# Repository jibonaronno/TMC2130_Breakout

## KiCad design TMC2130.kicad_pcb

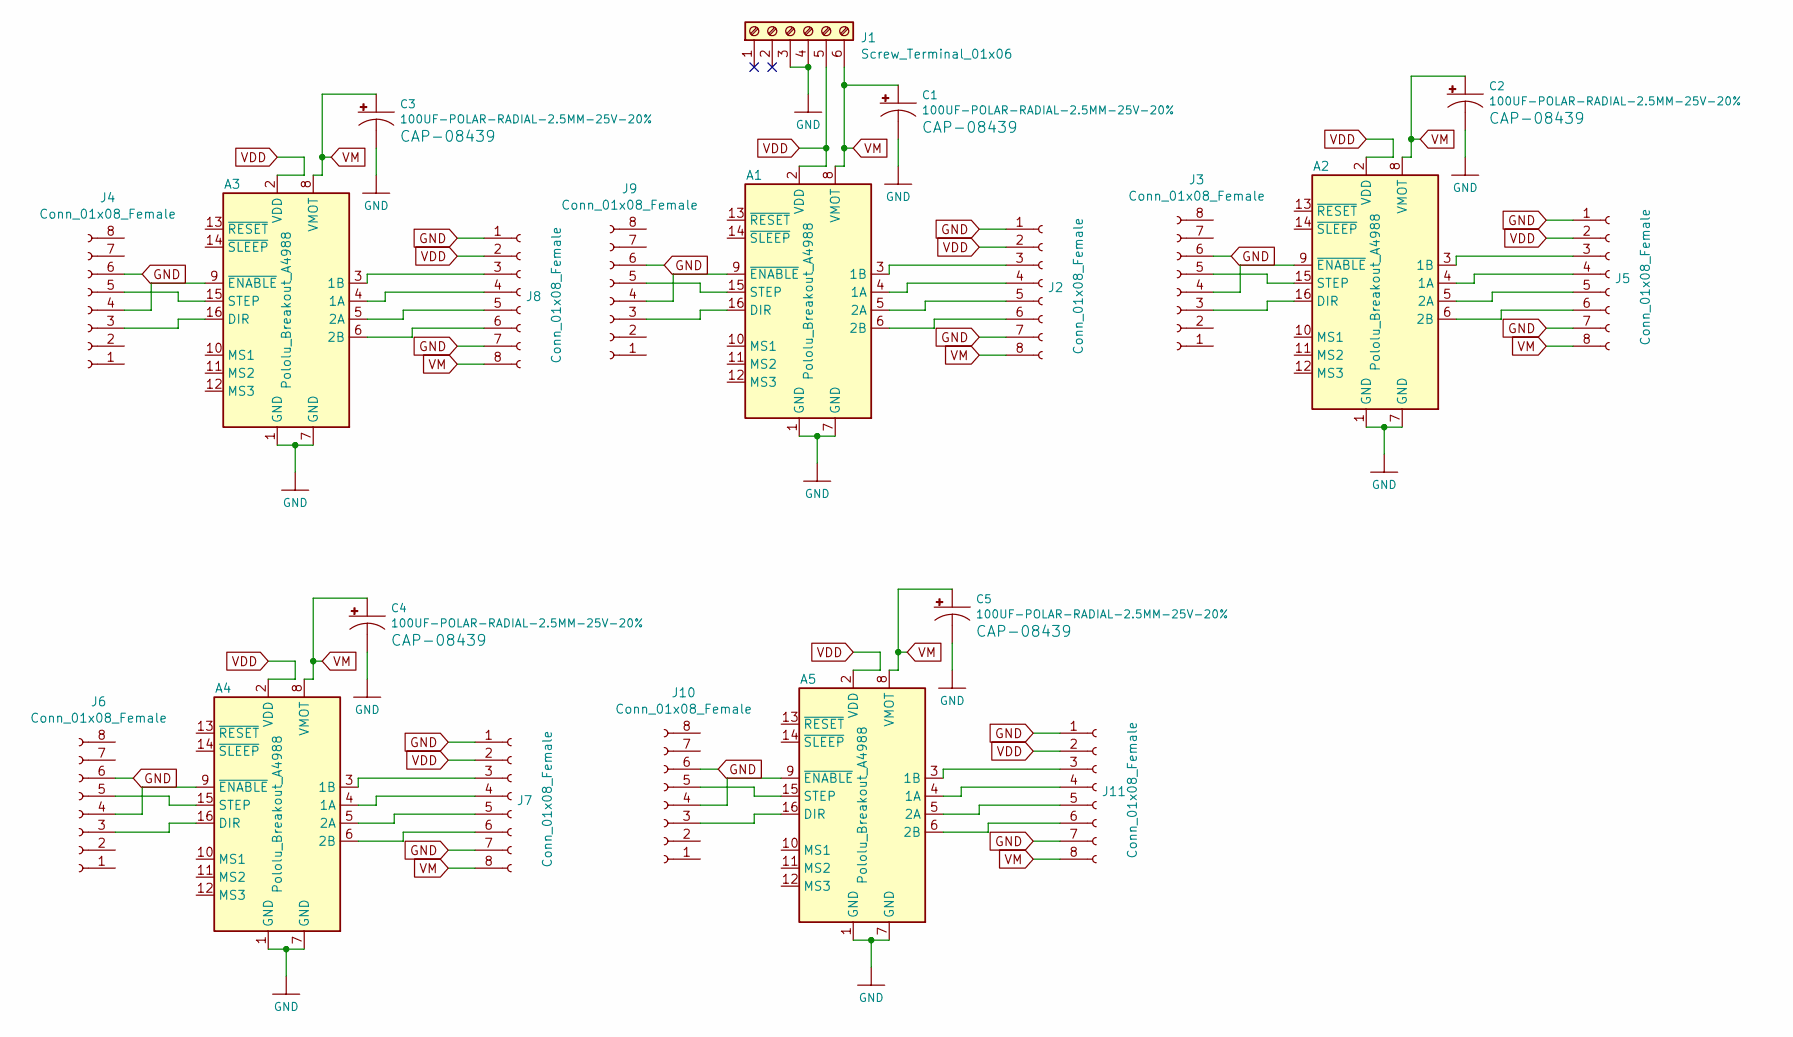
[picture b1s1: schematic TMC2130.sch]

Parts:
A1, A2, A3, A4, A5: Pololu_Breakout_A4988; Pololu_Breakout-16_15.2x20.3mm
C1, C2, C3, C4, C5: 100UF-POLAR-RADIAL-2.5MM-25V-20%; CPOL-RADIAL-2.5MM-6.5MM
J1: Screw_Terminal_01x06; TerminalBlock_MetzConnect_Type011_RT05506HBWC_1x06_P5.00mm_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
J2, J3, J4, J5, J6, J7, J8, J9, J10, J11: Conn_01x08_Female; JST_EH_B8B-EH-A_1x08_P2.50mm_Vertical

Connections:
GND: A1.1 (GND), A1.7 (GND), A2.1 (GND), A2.7 (GND), A3.1 (GND), A3.7 (GND), A4.1 (GND), A4.7 (GND), A5.1 (GND), A5.7 (GND), C1.2 (-), C2.2 (-), C3.2 (-), C4.2 (-), C5.2 (-), J1.3, J1.4, J2.1, J2.7, J3.6, J4.6, J5.1, J5.7, J6.6, J7.1, J7.7, J8.1, J8.7, J9.6, J10.6, J11.1, J11.7
unnamed: A1.3 (1B), J2.3
unnamed: A1.4 (1A), J2.4
unnamed: A1.5 (2A), J2.5
unnamed: A1.6 (2B), J2.6
unnamed: A1.9 (~ENABLE), J9.4
unnamed: A1.15 (STEP), J9.5
unnamed: A1.16 (DIR), J9.3
unnamed: A2.3 (1B), J5.3
unnamed: A2.4 (1A), J5.4
unnamed: A2.5 (2A), J5.5
unnamed: A2.6 (2B), J5.6
unnamed: A2.9 (~ENABLE), J3.4
unnamed: A2.15 (STEP), J3.5
unnamed: A2.16 (DIR), J3.3
unnamed: A3.3 (1B), J8.3
unnamed: A3.4 (1A), J8.4
unnamed: A3.5 (2A), J8.5
unnamed: A3.6 (2B), J8.6
unnamed: A3.9 (~ENABLE), J4.4
unnamed: A3.15 (STEP), J4.5
unnamed: A3.16 (DIR), J4.3
unnamed: A4.3 (1B), J7.3
unnamed: A4.4 (1A), J7.4
unnamed: A4.5 (2A), J7.5
unnamed: A4.6 (2B), J7.6
unnamed: A4.9 (~ENABLE), J6.4
unnamed: A4.15 (STEP), J6.5
unnamed: A4.16 (DIR), J6.3
unnamed: A5.3 (1B), J11.3
unnamed: A5.4 (1A), J11.4
unnamed: A5.5 (2A), J11.5
unnamed: A5.6 (2B), J11.6
unnamed: A5.9 (~ENABLE), J10.4
unnamed: A5.15 (STEP), J10.5
unnamed: A5.16 (DIR), J10.3
VDD: A1.2 (VDD), A2.2 (VDD), A3.2 (VDD), A4.2 (VDD), A5.2 (VDD), J1.5, J2.2, J5.2, J7.2, J8.2, J11.2
VM: A1.8 (VMOT), A2.8 (VMOT), A3.8 (VMOT), A4.8 (VMOT), A5.8 (VMOT), C1.1 (+), C2.1 (+), C3.1 (+), C4.1 (+), C5.1 (+), J1.6, J2.8, J5.8, J7.8, J8.8, J11.8

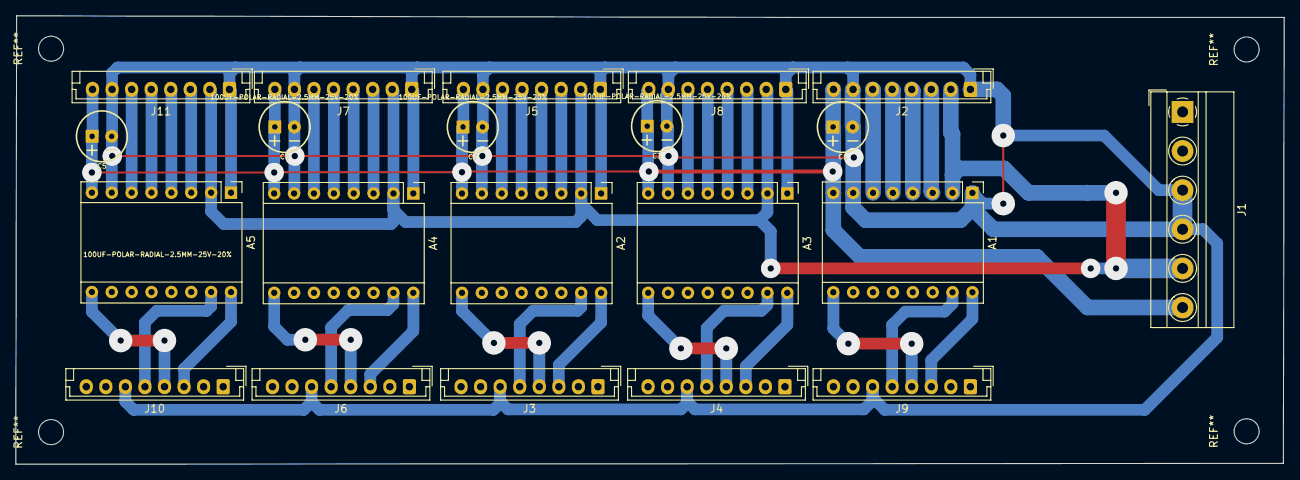
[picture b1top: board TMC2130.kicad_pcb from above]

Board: 2 copper layers, 162.1 x 57.3 mm, 21 parts (0 on the bottom side), 38 nets.

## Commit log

2020-09-25 FYSETC TMC2130 5 module breakout board kicad pcb
